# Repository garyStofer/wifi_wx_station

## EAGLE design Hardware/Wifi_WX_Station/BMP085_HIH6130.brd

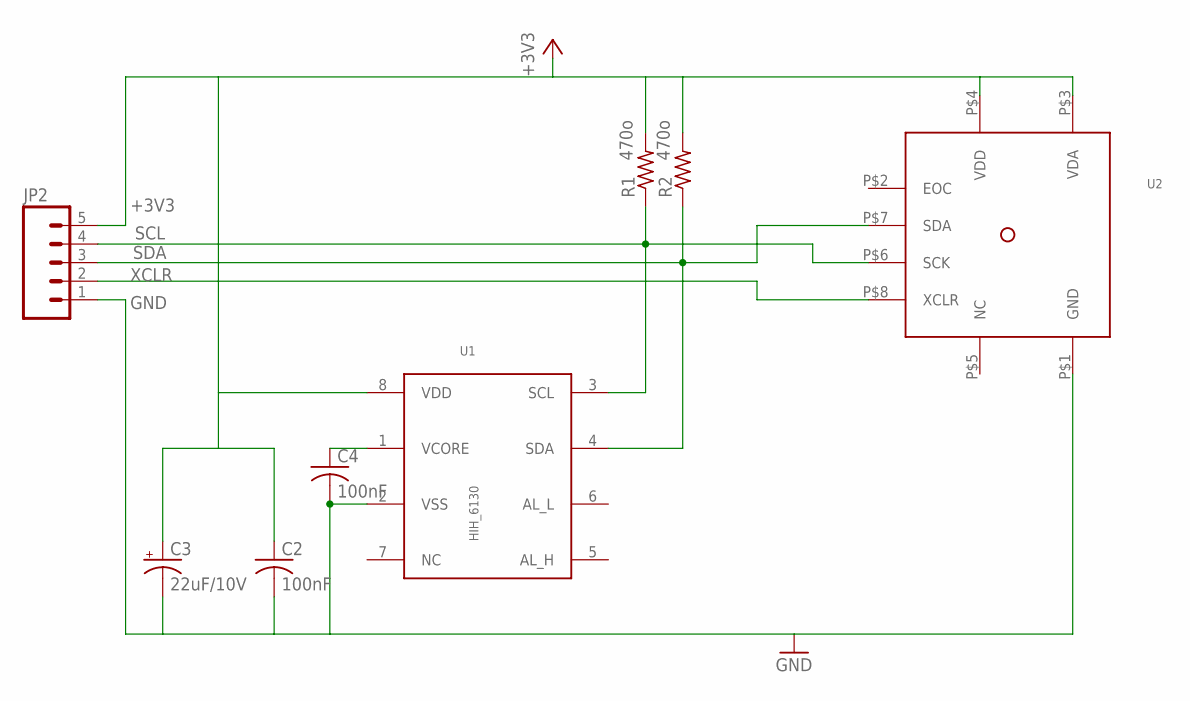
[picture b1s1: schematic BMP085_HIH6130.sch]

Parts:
C2, C4: 100nF; C0805K
C3: 22uF/10V; SMC_B
JP2: M05PTH; 1X05
R1, R2: 470o; R0603
U1: HIH_6130; SOIC8
U2: BMP085; LCC8

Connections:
+3V3: C2.1, C3.+, JP2.5, R1.2, R2.2, U1.8 (VDD), U2.P$3 (VDA), U2.P$4 (VDD)
GND: C2.2, C3.-, C4.2, JP2.1, U1.2 (VSS), U2.P$1 (GND)
unnamed: C4.1, U1.1 (VCORE)
SCL: JP2.4, R1.1, U1.3 (SCL), U2.P$6 (SCK)
SDA: JP2.3, R2.1, U1.4 (SDA), U2.P$7 (SDA)
XCLR: JP2.2, U2.P$8 (XCLR)

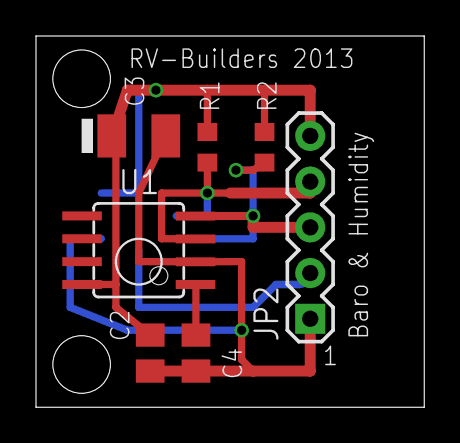
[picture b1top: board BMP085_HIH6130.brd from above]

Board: 2 copper layers, 21.6 x 20.6 mm, 8 parts (1 on the bottom side), 6 nets.

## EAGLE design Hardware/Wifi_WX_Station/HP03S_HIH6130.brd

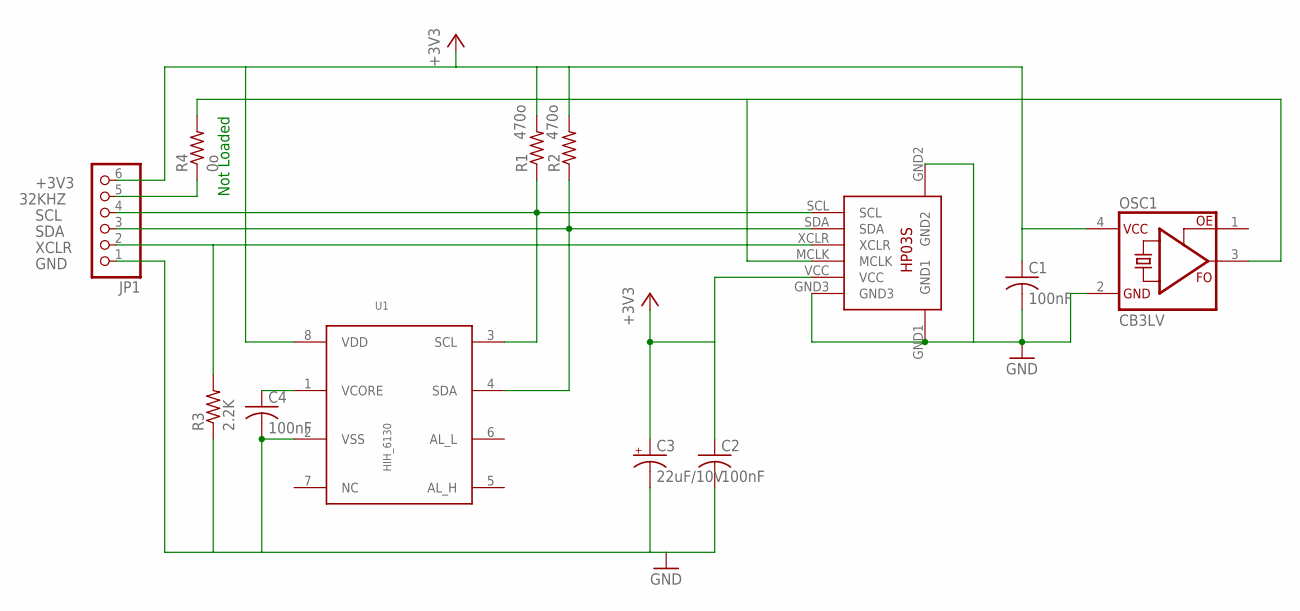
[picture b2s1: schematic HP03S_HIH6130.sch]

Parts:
C1: 100nF; C0805
C2, C4: 100nF; C0805K
C3: 22uF/10V; SMC_B
JP1: PINHD-1X6; 1X06
OSC1: CB3LV; SMD7.5X5MM
R1, R2: 470o; R0603
R3: 2.2K; R0603
R4: 0o; R0603
U1: HIH_6130; SOIC8
U2: HP03S

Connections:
32KHZ: JP1.5, R4.1
+3V3: C1.1, C2.1, C3.+, JP1.6, OSC1.4 (VCC), R1.2, R2.2, U1.8 (VDD), U2.VCC
GND: C1.2, C2.2, C3.-, C4.2, JP1.1, OSC1.2 (GND), R3.1, U1.2 (VSS), U2.GND1, U2.GND2, U2.GND3
unnamed: C4.1, U1.1 (VCORE)
RTCCLK: OSC1.3 (FO), R4.2, U2.MCLK
SCL: JP1.4, R1.1, U1.3 (SCL), U2.SCL
SDA: JP1.3, R2.1, U1.4 (SDA), U2.SDA
XCLR: JP1.2, R3.2, U2.XCLR

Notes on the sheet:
Not Loaded

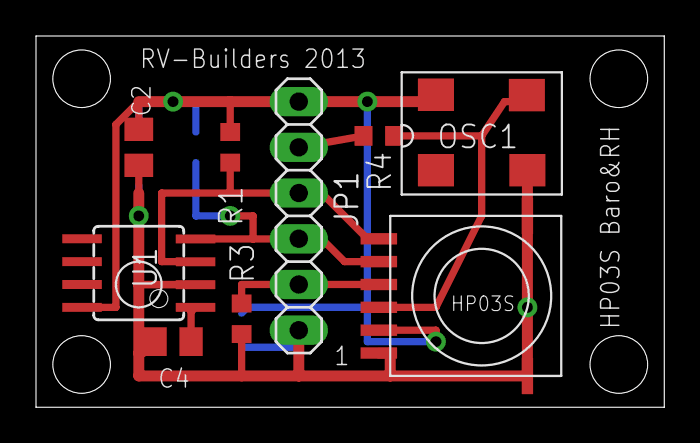
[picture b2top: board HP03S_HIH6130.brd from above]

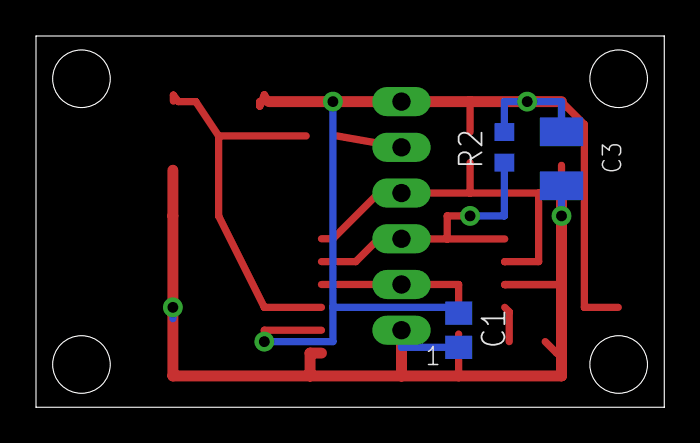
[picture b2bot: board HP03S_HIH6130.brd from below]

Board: 2 copper layers, 34.9 x 20.6 mm, 12 parts (3 on the bottom side), 8 nets.

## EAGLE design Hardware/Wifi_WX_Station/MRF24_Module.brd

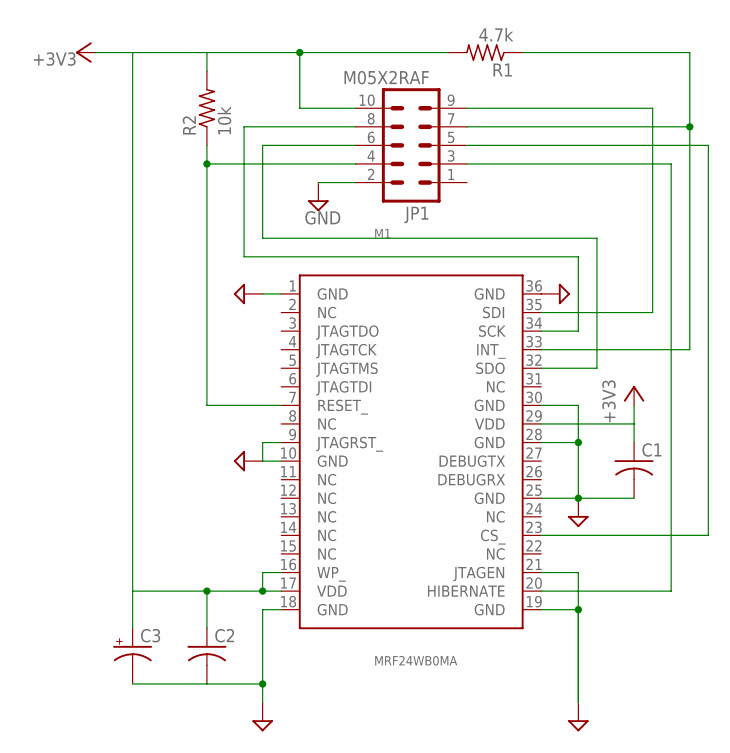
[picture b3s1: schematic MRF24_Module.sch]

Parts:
C1, C2: C-USC0805; C0805
C3: CPOL-USR/2012-12R; R/2012-12R
JP1: M05X2RAF; 2X5-RAF
M1: MRF24WB0MA; MRF24W
R1: 4.7k; R0603
R2: 10k; R0603

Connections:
+3V3: C1.1, C2.1, C3.+, JP1.10, M1.16 (WP_), M1.17 (VDD), M1.29 (VDD), R1.2, R2.2
CS_: JP1.5, M1.23 (CS_)
GND: C1.2, C2.2, C3.-, JP1.2, M1.1 (GND), M1.9 (JTAGRST_), M1.10 (GND), M1.18 (GND), M1.19 (GND), M1.21 (JTAGEN), M1.25 (GND), M1.28 (GND), M1.30 (GND), M1.36 (GND)
HIBER: JP1.3, M1.20 (HIBERNATE)
INT_: JP1.7, M1.33 (INT_), R1.1
RESET_: JP1.4, M1.7 (RESET_), R2.1
SCK: JP1.8, M1.34 (SCK)
SDI: JP1.9, M1.35 (SDI)
SDO: JP1.6, M1.32 (SDO)

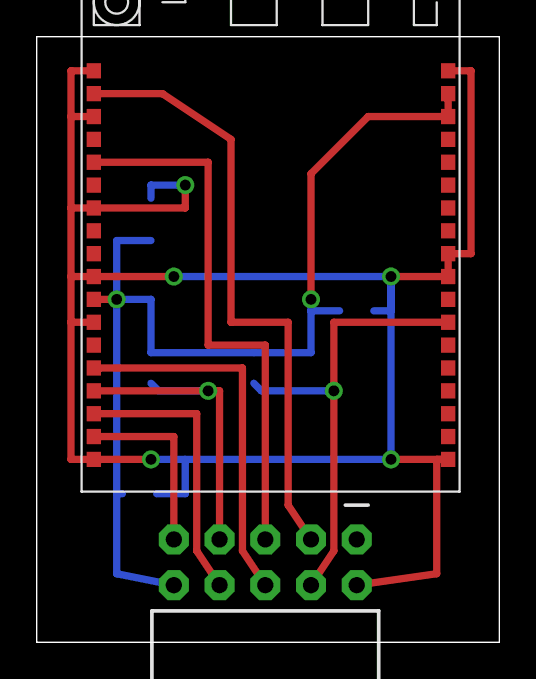
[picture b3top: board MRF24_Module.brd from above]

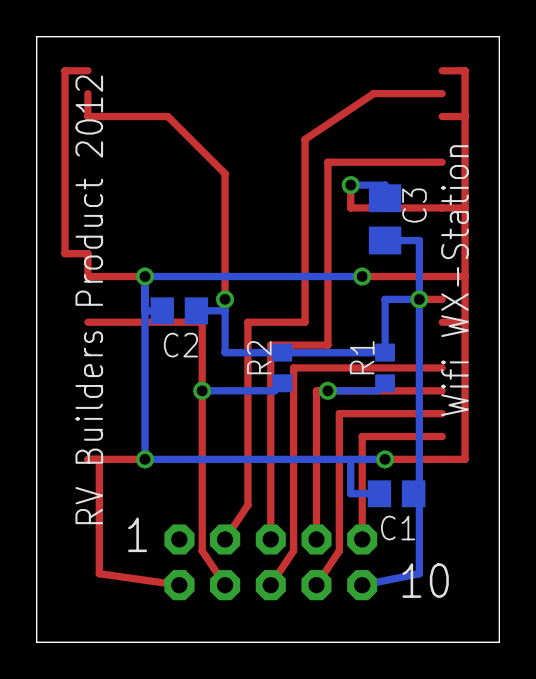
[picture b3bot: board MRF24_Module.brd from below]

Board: 2 copper layers, 25.7 x 33.6 mm, 7 parts (5 on the bottom side), 9 nets.

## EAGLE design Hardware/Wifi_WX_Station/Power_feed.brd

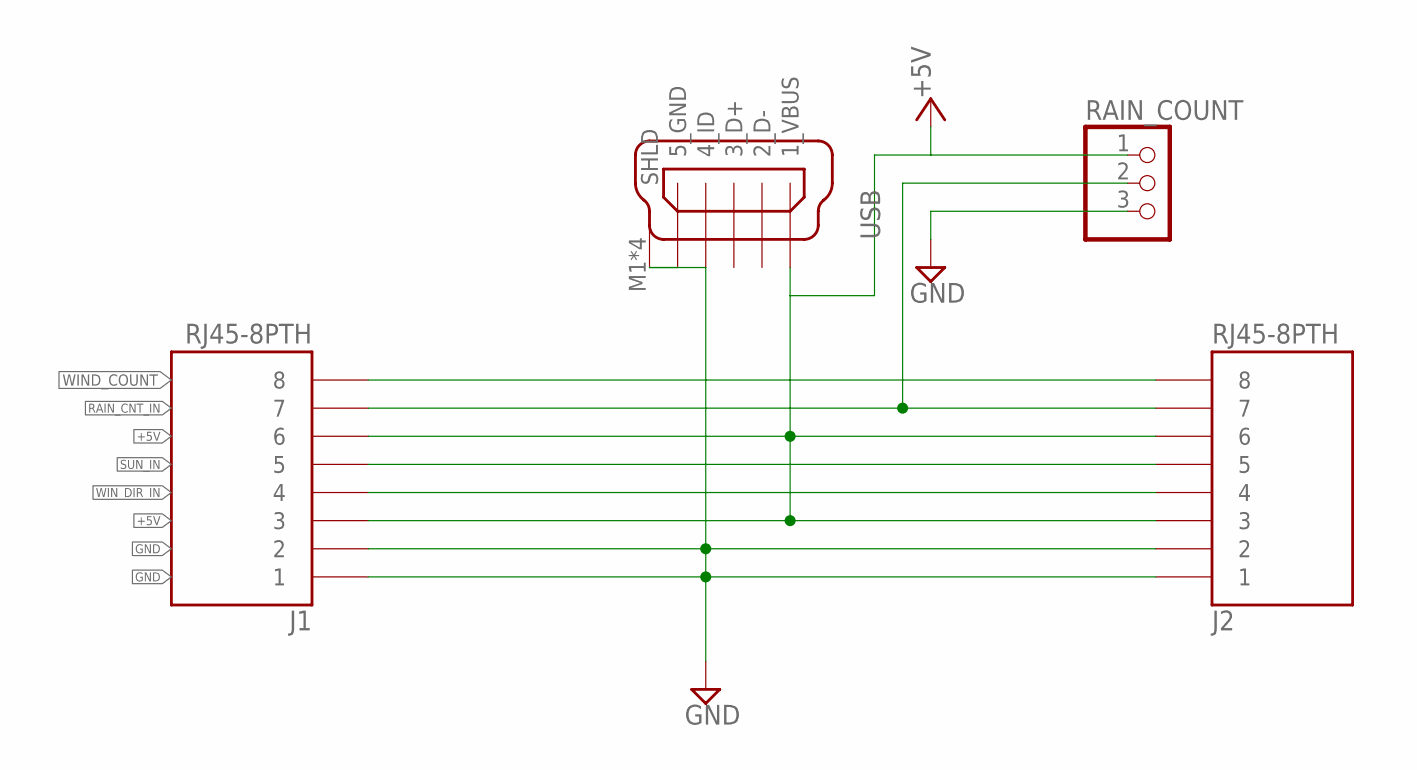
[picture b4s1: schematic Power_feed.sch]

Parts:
J1, J2: RJ45-8PTH; RJ45-8
RAIN_COUNT: PINHD-1X3; 1X03
USB: MINI-USB-32005-301; 32005-301

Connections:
+5V: J1.3, J1.6, J2.3, J2.6, RAIN_COUNT.1, USB.1_VBUS
GND: J1.1, J1.2, J2.1, J2.2, RAIN_COUNT.3, USB.5_USB_GND (5_GND), USB.M1 (SHLD), USB.M2 (SHLD), USB.M3 (SHLD), USB.M4 (SHLD)
RAIN_CNT_IN: J1.7, J2.7, RAIN_COUNT.2
SUN_IN: J1.5, J2.5
WIND_COUNT: J1.8, J2.8
WIN_DIR_IN: J1.4, J2.4

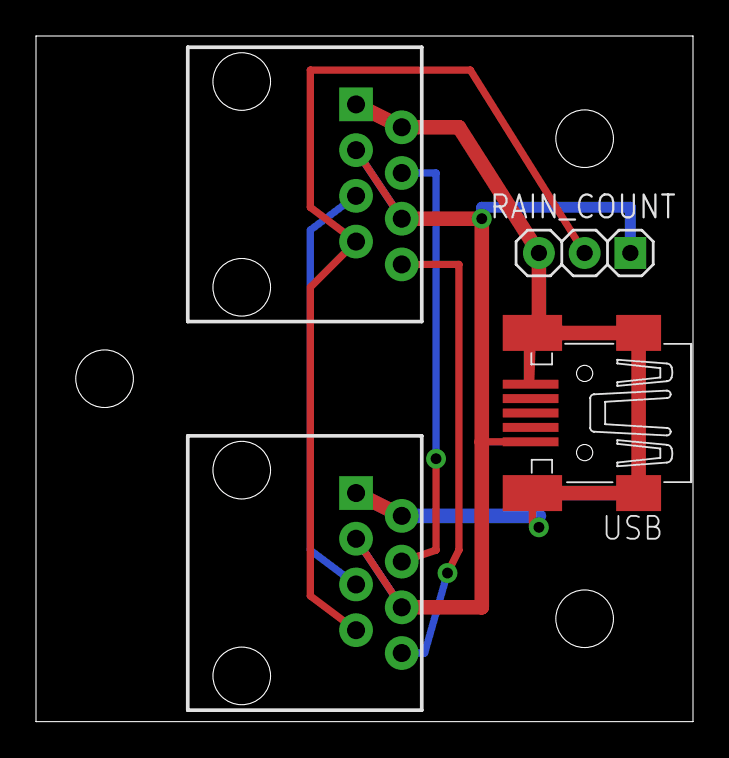
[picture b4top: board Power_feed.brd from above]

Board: 2 copper layers, 36.5 x 38.1 mm, 4 parts (0 on the bottom side), 6 nets.

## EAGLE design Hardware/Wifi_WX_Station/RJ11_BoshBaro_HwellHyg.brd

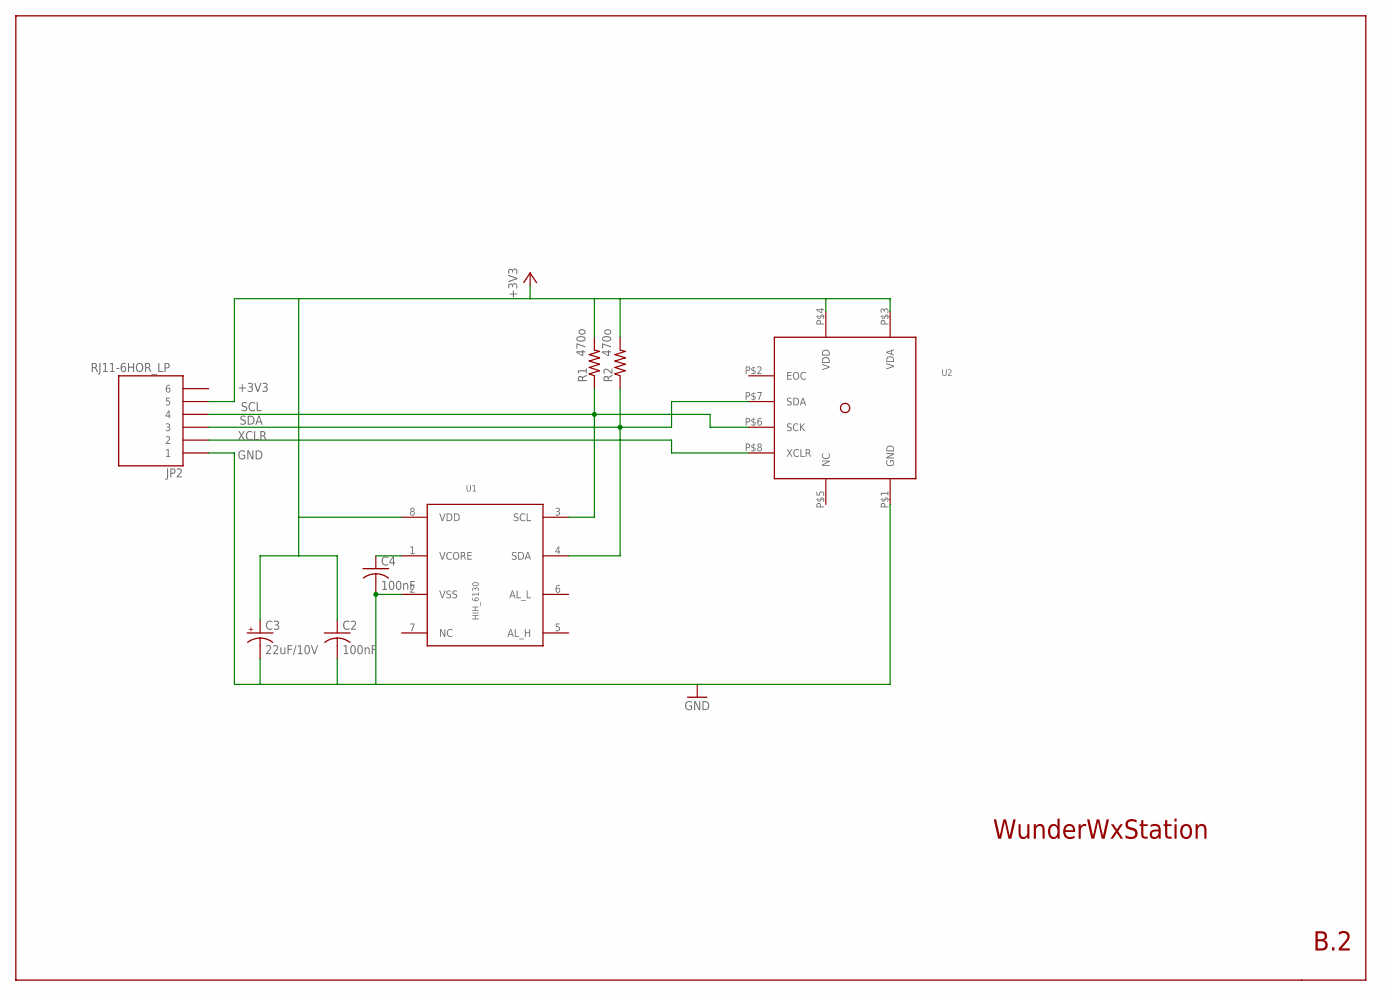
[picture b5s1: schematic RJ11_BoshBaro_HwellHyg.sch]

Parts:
C2, C4: 100nF; C0805K
C3: 22uF/10V; SMC_B
JP2: RJ11-6HOR_LP; RJ11_HOR_LP
R1, R2: 470o; R0603
U1: HIH_6130; SOIC8
U2: BMP085; LCC8

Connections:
+3V3: C2.1, C3.+, JP2.P$5 (5), R1.2, R2.2, U1.8 (VDD), U2.P$3 (VDA), U2.P$4 (VDD)
GND: C2.2, C3.-, C4.2, JP2.P$1 (1), U1.2 (VSS), U2.P$1 (GND)
unnamed: C4.1, U1.1 (VCORE)
SCL: JP2.P$4 (4), R1.1, U1.3 (SCL), U2.P$6 (SCK)
SDA: JP2.P$3 (3), R2.1, U1.4 (SDA), U2.P$7 (SDA)
XCLR: JP2.P$2 (2), U2.P$8 (XCLR)

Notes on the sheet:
WunderWxStation
B.2

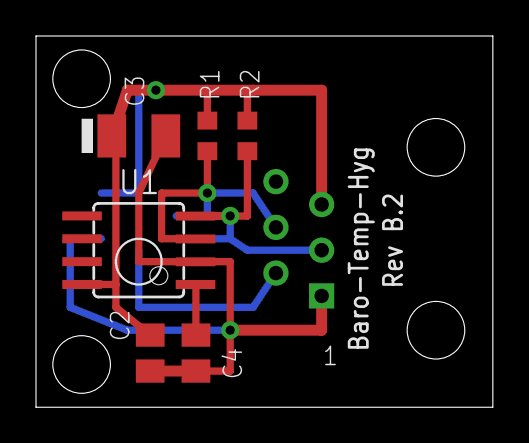
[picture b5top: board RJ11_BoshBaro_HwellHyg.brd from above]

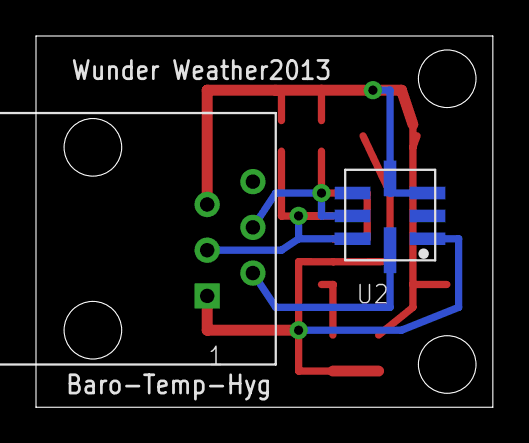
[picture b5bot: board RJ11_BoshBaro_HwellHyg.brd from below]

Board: 2 copper layers, 25.4 x 20.6 mm, 8 parts (2 on the bottom side), 6 nets.

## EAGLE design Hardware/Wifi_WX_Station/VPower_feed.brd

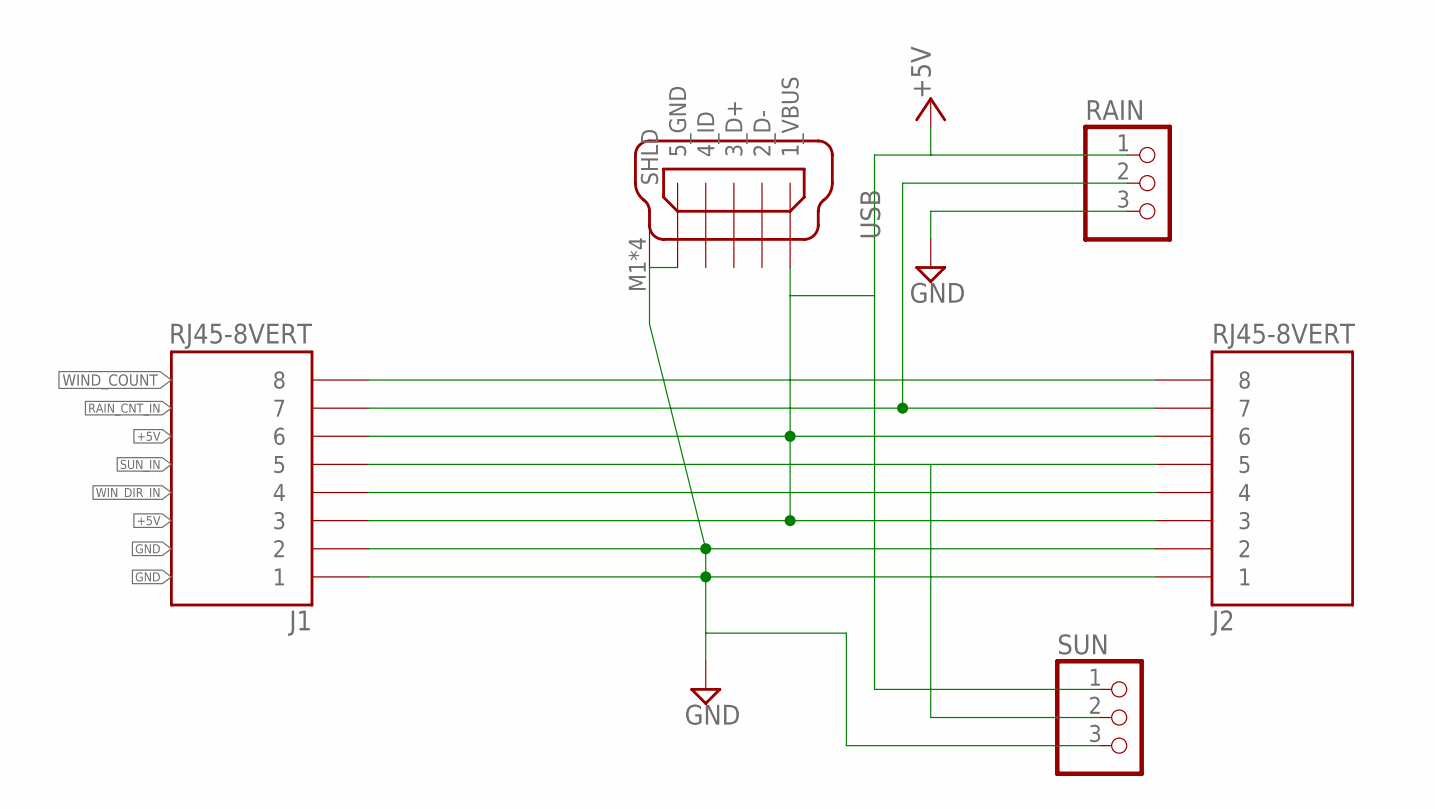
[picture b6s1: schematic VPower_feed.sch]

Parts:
J1, J2: RJ45-8VERT; RJ45_VERT
RAIN: PINHD-1X3MOLEX_KK; 1X3_MOLEX_KK
SUN: PINHD-1X3MOLEX_KK; 1X3_MOLEX_KK
USB: MINI-USB-32005-301; 32005-301

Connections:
+5V: J1.P$3 (3), J1.P$6 (6), J2.P$3 (3), J2.P$6 (6), RAIN.1, SUN.1, USB.1_VBUS
GND: J1.P$1 (1), J1.P$2 (2), J2.P$1 (1), J2.P$2 (2), RAIN.3, SUN.3, USB.5_USB_GND (5_GND), USB.M1 (SHLD), USB.M2 (SHLD), USB.M3 (SHLD), USB.M4 (SHLD)
RAIN_CNT_IN: J1.P$7 (7), J2.P$7 (7), RAIN.2
SUN_IN: J1.P$5 (5), J2.P$5 (5), SUN.2
WIND_COUNT: J1.P$8 (8), J2.P$8 (8)
WIN_DIR_IN: J1.P$4 (4), J2.P$4 (4)

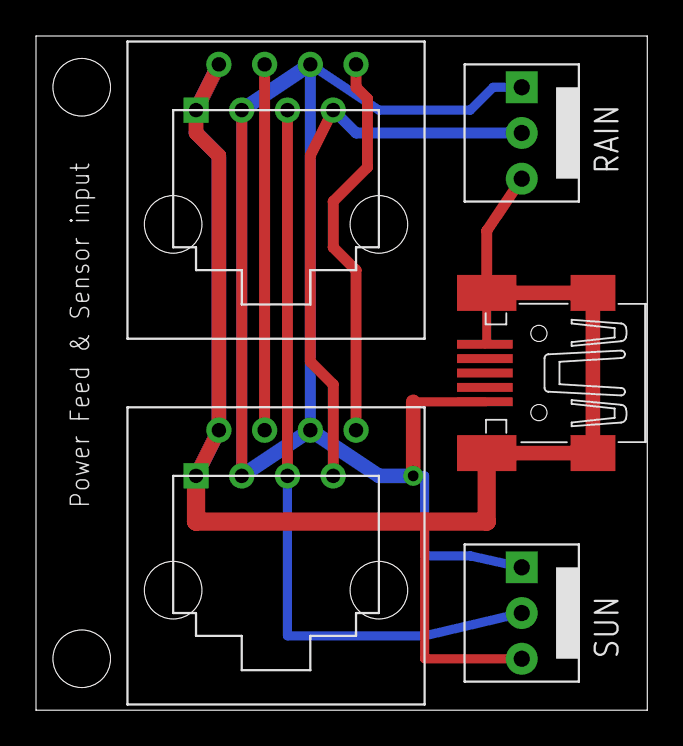
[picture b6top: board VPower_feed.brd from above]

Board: 2 copper layers, 34.0 x 37.5 mm, 5 parts (0 on the bottom side), 6 nets.

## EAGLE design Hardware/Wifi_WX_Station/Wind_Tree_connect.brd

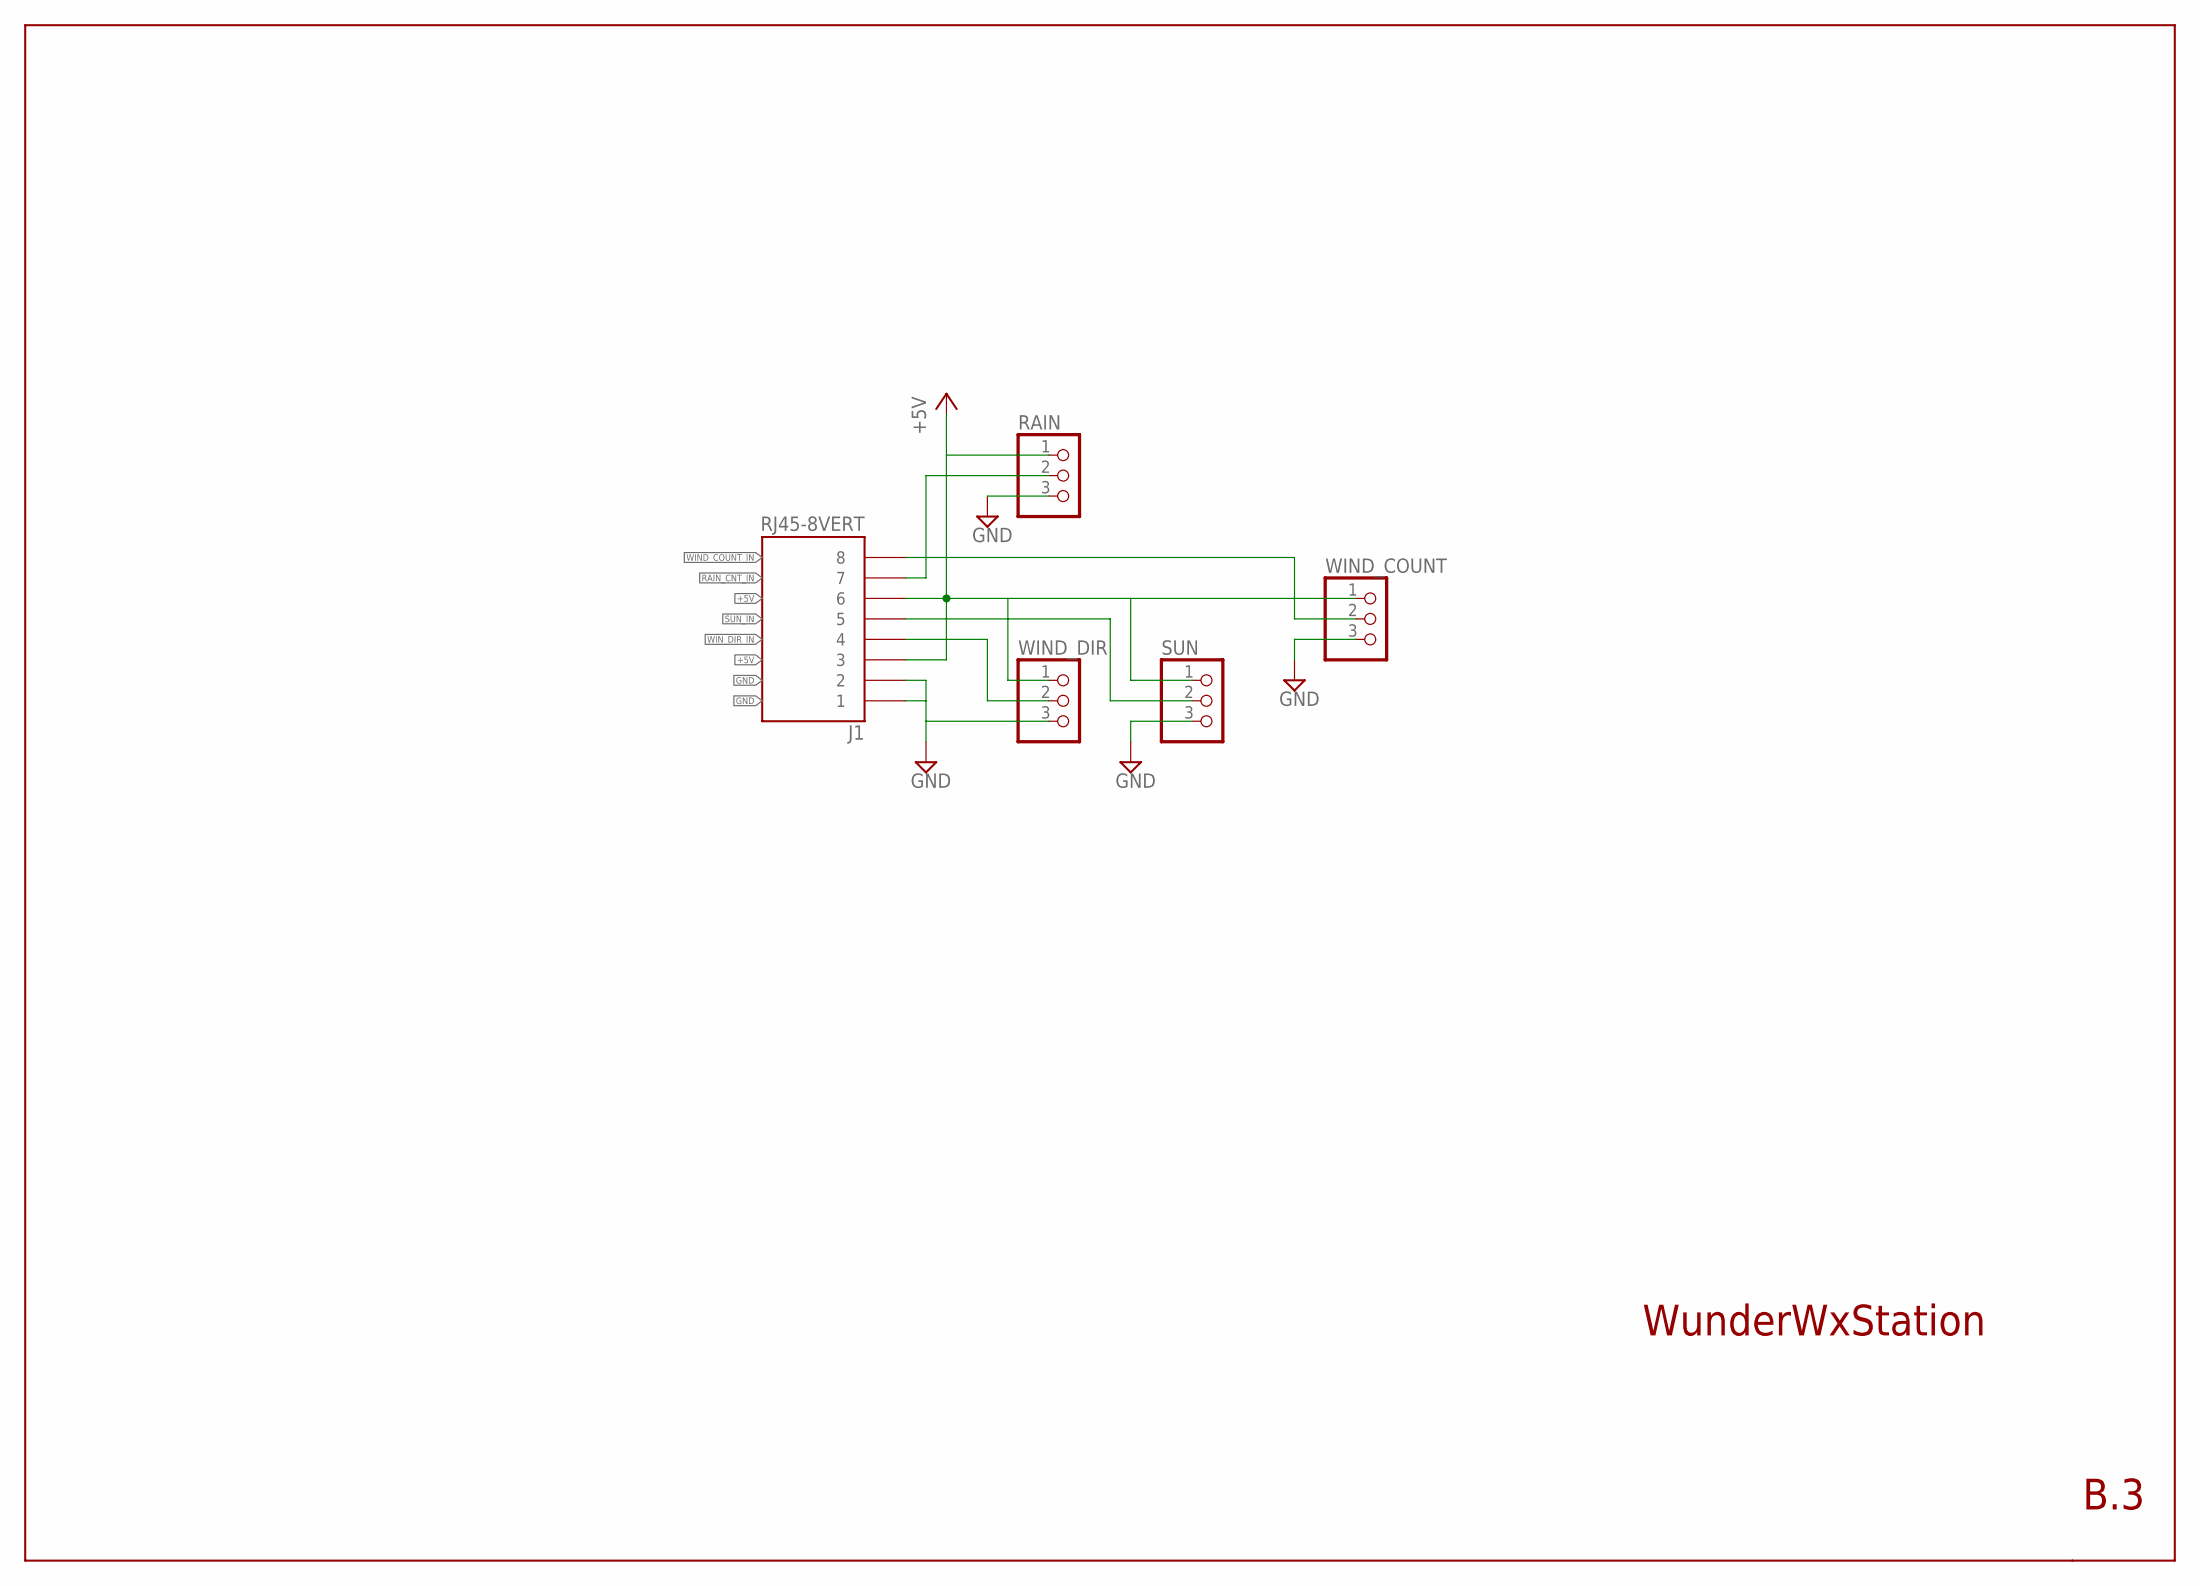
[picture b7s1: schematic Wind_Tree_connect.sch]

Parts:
J1: RJ45-8VERT; RJ45_VERT
RAIN: PINHD-1X3; 1X03
SUN: PINHD-1X3; 1X03
WIND_COUNT: PINHD-1X3; 1X03
WIND_DIR: PINHD-1X3; 1X03

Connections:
+5V: J1.P$3 (3), J1.P$6 (6), RAIN.1, SUN.1, WIND_COUNT.1, WIND_DIR.1
GND: J1.P$1 (1), J1.P$2 (2), RAIN.3, SUN.3, WIND_COUNT.3, WIND_DIR.3
RAIN_CNT_IN: J1.P$7 (7), RAIN.2
SUN_IN: J1.P$5 (5), SUN.2
WIND_COUNT_IN: J1.P$8 (8), WIND_COUNT.2
WIN_DIR_IN: J1.P$4 (4), WIND_DIR.2

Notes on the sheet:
WunderWxStation
B.3

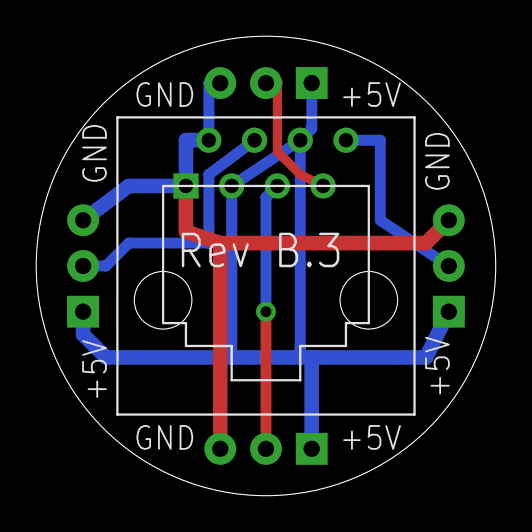
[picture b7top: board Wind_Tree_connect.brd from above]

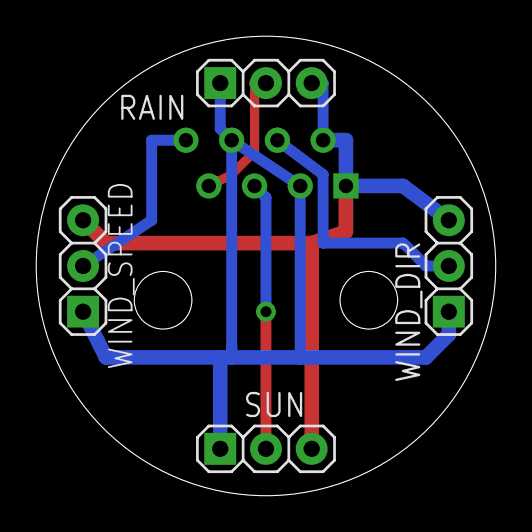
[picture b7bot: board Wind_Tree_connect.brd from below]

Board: 2 copper layers, 25.5 x 25.5 mm, 5 parts (4 on the bottom side), 6 nets.

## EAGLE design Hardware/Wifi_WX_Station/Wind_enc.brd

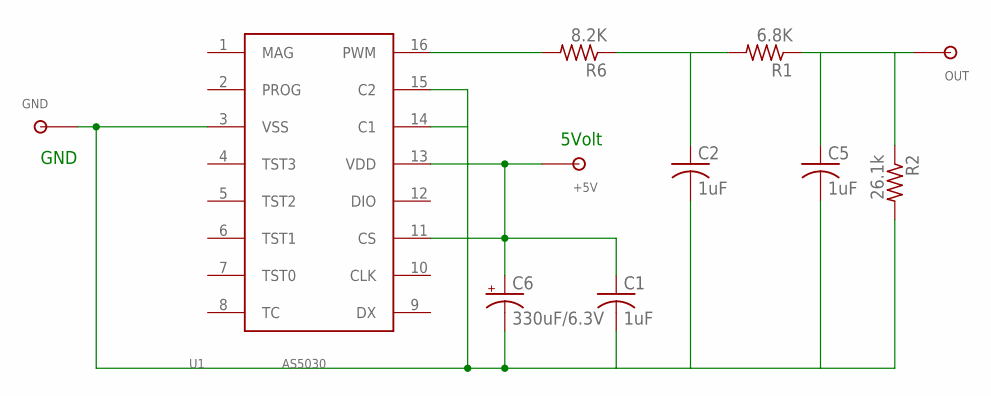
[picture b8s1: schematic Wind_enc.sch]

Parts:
+5V: TPSOL; TP_SOL
C1, C2, C5: 1uF; C0805K
C6: 330uF/6.3V; SMC_D
GND: TPSOL; TP_SOL
OUT: TPSOL; TP_SOL
R1: 6.8K; R0603
R2: 26.1k; R0603
R6: 8.2K; R0603
U1: AS5030; TSSOP16

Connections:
unnamed: +5V.P$1, C1.1, C6.+, U1.11 (CS), U1.13 (VDD)
unnamed: C1.2, C2.2, C5.2, C6.-, GND.P$1, R2.2, U1.3 (VSS), U1.14 (C1), U1.15 (C2)
unnamed: C5.1, OUT.P$1, R1.1, R2.1
unnamed: C2.1, R1.2, R6.1
unnamed: R6.2, U1.16 (PWM)

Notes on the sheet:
5Volt
GND
